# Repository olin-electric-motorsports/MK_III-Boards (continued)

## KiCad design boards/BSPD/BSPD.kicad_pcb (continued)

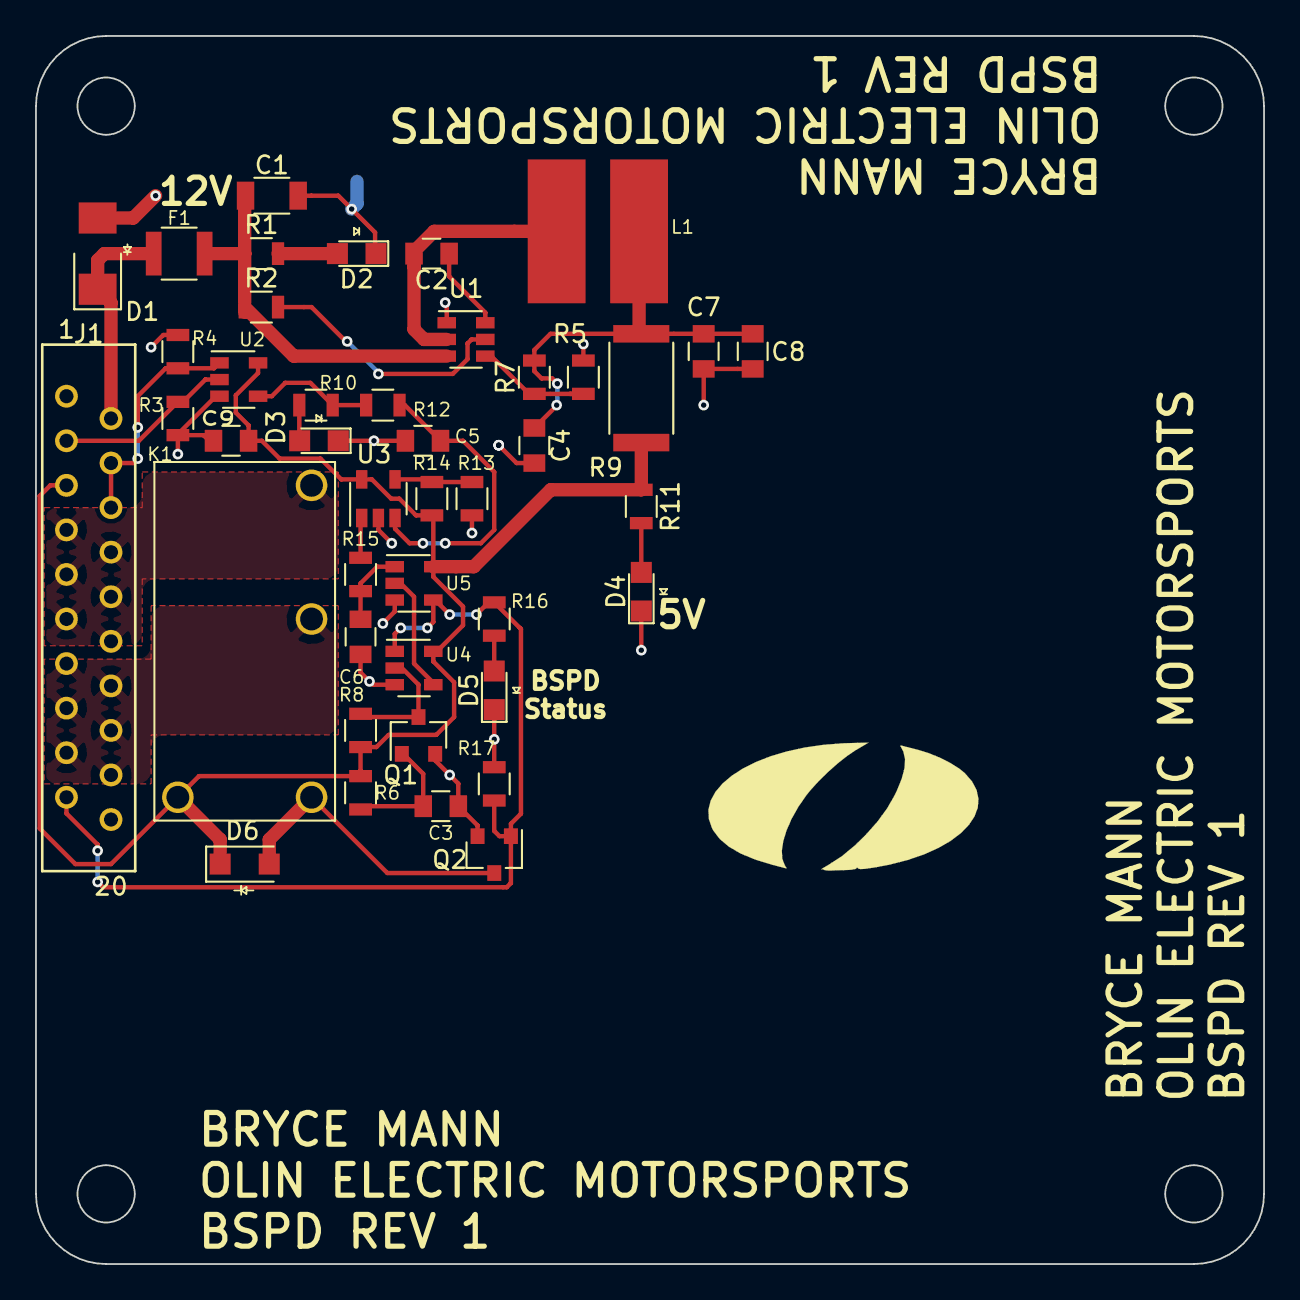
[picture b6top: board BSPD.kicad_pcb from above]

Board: 2 copper layers, 70.0 x 70.0 mm, 43 parts (0 on the bottom side), 27 nets.

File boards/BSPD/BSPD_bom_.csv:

Component,Description,Part,References,Value,Footprint,Quantity Per PCB,Datasheet,Package,MPN,MFN,PurchasingLink,MNF
1,Cap 50V 0.1uF 10% 0805,C_0.1uF,C2 C3 C8 C9,C_0.1uF,C_0805_OEM,4,http://datasheets.avx.com/X7RDielectric.pdf,Value,478-3352-1-ND,Digi-Key,https://www.digikey.com/products/en?keywords=478-3352-1-ND,
2,CAP CER 10UF 10V X5R 0805,C_10uF,C5,C_10uF,C_0805_OEM,1,http://datasheets.avx.com/cx5r.pdf,Value,478-5167-1-ND,Digi-Key,https://www.digikey.com/product-detail/en/avx-corporation/08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,
3,CAP CER 1UF 25V X7R 0805,C_1uF,C6 C7,C_1uF,C_0805_OEM,2,http://datasheets.avx.com/X7RDielectric.pdf,Value,478-10487-1-ND,Digi-Key,https://www.digikey.com/product-detail/en/avx-corporation/08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,
4,Unpolarized capacitor,C_22uF,C1,C_22uF,C_1206_OEM,1,http://www.samsungsem.com/kr/support/product-search/mlcc/__i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,Value,1276-2725-1-ND,Digi-Key,https://www.digikey.com/products/en?keywords=1276-2725-1-ND,
5,CAP CER 47UF 6.3V X5R 0805,C_47uF,C4,C_47uF,C_0805_OEM,1,http://www.yuden.co.jp/productdata/catalog/en/mlcc_all_e.pdf,Value,587-4280-1-ND,Digi-Key,https://www.digikey.com/product-detail/en/taiyo-yuden/JMK212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,
6,DIODE SCHOTTKY 100V 1A SOD123,D_Schottky_SOD123,D6,D_Schottky_SOD123,D_SOD-123W_OEM,1,https://assets.nexperia.com/documents/data-sheet/PMEG10010ELR.pdf,,1727-2394-1-ND,Digi-Key,https://www.digikey.com/product-detail/en/nexperia-usa-inc/P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,
7,DIODE ZENER 18V 5W DO214AA,D_Zener_18V,D1,D_Zener_18V,DO-214AA,1,http://www.mccsemi.com/up_pdf/SMBJ5338B-SMBJ5388B(SMB).pdf,DO-214AA (SMB),SMBJ5355B-TPMSCT-ND,Digi-Key,https://www.digikey.com/products/en?keywords=SMBJ5355B-TPMSCT-ND,
8,LED_0805,LED_0805,D2 D3 D4 D5,LED_0805,LED_0805_OEM,4,http://www.osram-os.com/Graphics/XPic9/00078860_0.pdf,Value,475-1410-1-ND,Digi-Key,https://www.digikey.com/products/en?keywords=475-1410-1-ND,
9,PTC Fuse 16V 500mA,F_500mA_16V,F1,F_500mA_16V,Fuse_1210,1,https://belfuse.com/resources/CircuitProtection/datasheets/0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,Value,507-1786-1-ND,Digi-Key,https://www.digikey.com/product-detail/en/bel-fuse-inc/0ZCH0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,
10,connector micromatch female RA 20,micromatch_female_RA_20,J1,micromatch_female_RA_20,micromatch_female_ra_20,1,,Value,A99490CT-ND,Digi-Key,https://www.digikey.com/product-detail/en/te-connectivity-am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,
11,g5q power relay,G5Q-1A4-DC5-5V,K1,G5Q-1A4-DC5-5V,Relay_SPST_OMRON-G5Q-1A4_OEM,1,http://omronfs.omron.com/en_US/ecb/products/pdf/en-g5q.pdf,,Z3632-ND,Digi-Key,https://www.digikey.com/product-detail/en/omron-electronics-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,
12,Inductor 4.7uH 4.4A,L_4.7uH,L1,L_4.7uH,4.7uH_Inductor_OEM,1,https://product.tdk.com/info/en/documents/wdcatalog/withdraw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,Value,445-6583-1-ND,Digi-Key,https://www.digikey.com/product-detail/en/tdk-corporation/VL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,
13,"60V Vds, 0.115A Id, N-channel MOSFET, SOT-23",SSM3K333R,Q1 Q2,SSM3K333R,SOT-23F,2,https://drive.google.com/drive/folders/0B-V-iZf33Y4GNzhDQTJZanJRbVk,SOT-23-3 Flat Leads,SSM3K333RLFCT-ND,Digi-Key,https://www.digikey.com/product-detail/en/toshiba-semiconduc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,
14,Res 0 2512 3W Jumper,R_0_Jumper,R9,R_0_Jumper,R_2512_OEM,1,http://www.te.com/commerce/DocumentDelivery/DDEController?Ac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,Value,A121322CT-ND,Digi-Key,https://www.digikey.com/products/en?keywords=A121322CT-ND,
15,Res 100k 1%,R_100k,R3 R4 R8,R_100k,R_0805_OEM,3,http://www.yageo.com.tw/exep/pages/download/literatures/PYu-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,Value,311-100KCRCT-ND,Digi-Key,https://www.digikey.com/products/en?keywords=311-100KCRCT-ND,
16,Res 10k 1%,R_10k,R2 R5 R6 R13 R14 R15 R17,R_10k,R_0805_OEM,7,http://www.bourns.com/data/global/pdfs/CRS.pdf,Value,CRS0805-FX-1002ELFCT-ND,Digi-Key,https://www.digikey.com/products/en?keywords=CRS0805-FX-1002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,
17,Res 1k 1%,R_1k,R1,R_1k,R_0805_OEM,1,https://www.seielect.com/Catalog/SEI-rncp.pdf,Value,RNCP0805FTD1K00CT-ND,Digi-Key,https://www.digikey.com/products/en?keywords=RNCP0805FTD1K00CT-ND,
18,Res 200 5%,R_200,R10 R11 R16,R_200,R_0805_OEM,3,https://www.seielect.com/Catalog/SEI-RMCF_RMCP.pdf,Value,RMCF0805JT200RCT-ND,Digi-Key,https://www.digikey.com/products/en?keywords=RMCF0805JT200RCT-ND,
19,Res 55.1k 1%,R_55.1k,R7,R_55.1k,R_0805_OEM,1,http://www.yageo.com.tw/exep/pages/download/literatures/PYu-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,Value,311-51.1KCRCT-ND,Digi-Key,https://www.digikey.com/products/en?keywords=311-51.1KCRCT-ND,
20,Resistor,R_71.5k,R12,R_71.5k,R_0805_OEM,1,http://www.yageo.com/documents/recent/PYu-RC_Group_51_RoHS_L_8.pdf,Value,RC0805FR-0771K5L,Yageo,https://www.digikey.com/product-detail/en/yageo/RC0805FR-077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,
21,Op Amp in 5-pin package,MCP6001,U3,MCP6001,SOT-23-5_OEM,1,http://ww1.microchip.com/downloads/en/DeviceDoc/21733j.pdf,"SC-74A, SOT-753",MCP6001T-I/OT,,https://www.digikey.com/product-detail/en/microchip-technolo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,Microchip Technology
22,Single 2-Input Positive NOR-Gate,SN74LVC1G02,U4 U5,SN74LVC1G02,SOT-23-5_OEM,2,http://www.ti.com/lit/ds/symlink/sn74lvc1g02.pdf,"SC-74A, SOT-753",SN74LVC1G02DBVR,Texas Instruments,https://www.digikey.com/product-detail/en/texas-instruments/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,
23,Single 2-Input Positive-AND Gate,SN74LVC1G08,U2,SN74LVC1G08,SOT-23-5_OEM,1,http://www.ti.com/lit/ds/symlink/sn74lvc1g08.pdf,"SC-74A, SOT-753",SN74LVC1G08DBVR,Texas Instruments,https://www.digikey.com/product-detail/en/texas-instruments/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,
24,4.5V - 17V Input 1A Synchronous Buck Converter,TPS561201,U1,TPS561201,SOT-23-6_OEM,1,http://www.ti.com/lit/ds/symlink/tps561201.pdf,Value,TPS561201,Digi-Key,https://www.digikey.com/products/en?keywords=296-46928-1-ND,





Component Groups:,24
Component Count:,43
Fitted Components:,43
Number of PCBs:,1
Total components:,43
Schematic Version:,
Schematic Date:,
BoM Date:,Mon 05 Feb 2018 09:23:43 PM EST
Schematic Source:,/home/bryce/Desktop/Formula/MK_III-Boards/boards/BSPD/BSPD.sch
KiCad Version:,Eeschema 4.0.2+dfsg1-stable

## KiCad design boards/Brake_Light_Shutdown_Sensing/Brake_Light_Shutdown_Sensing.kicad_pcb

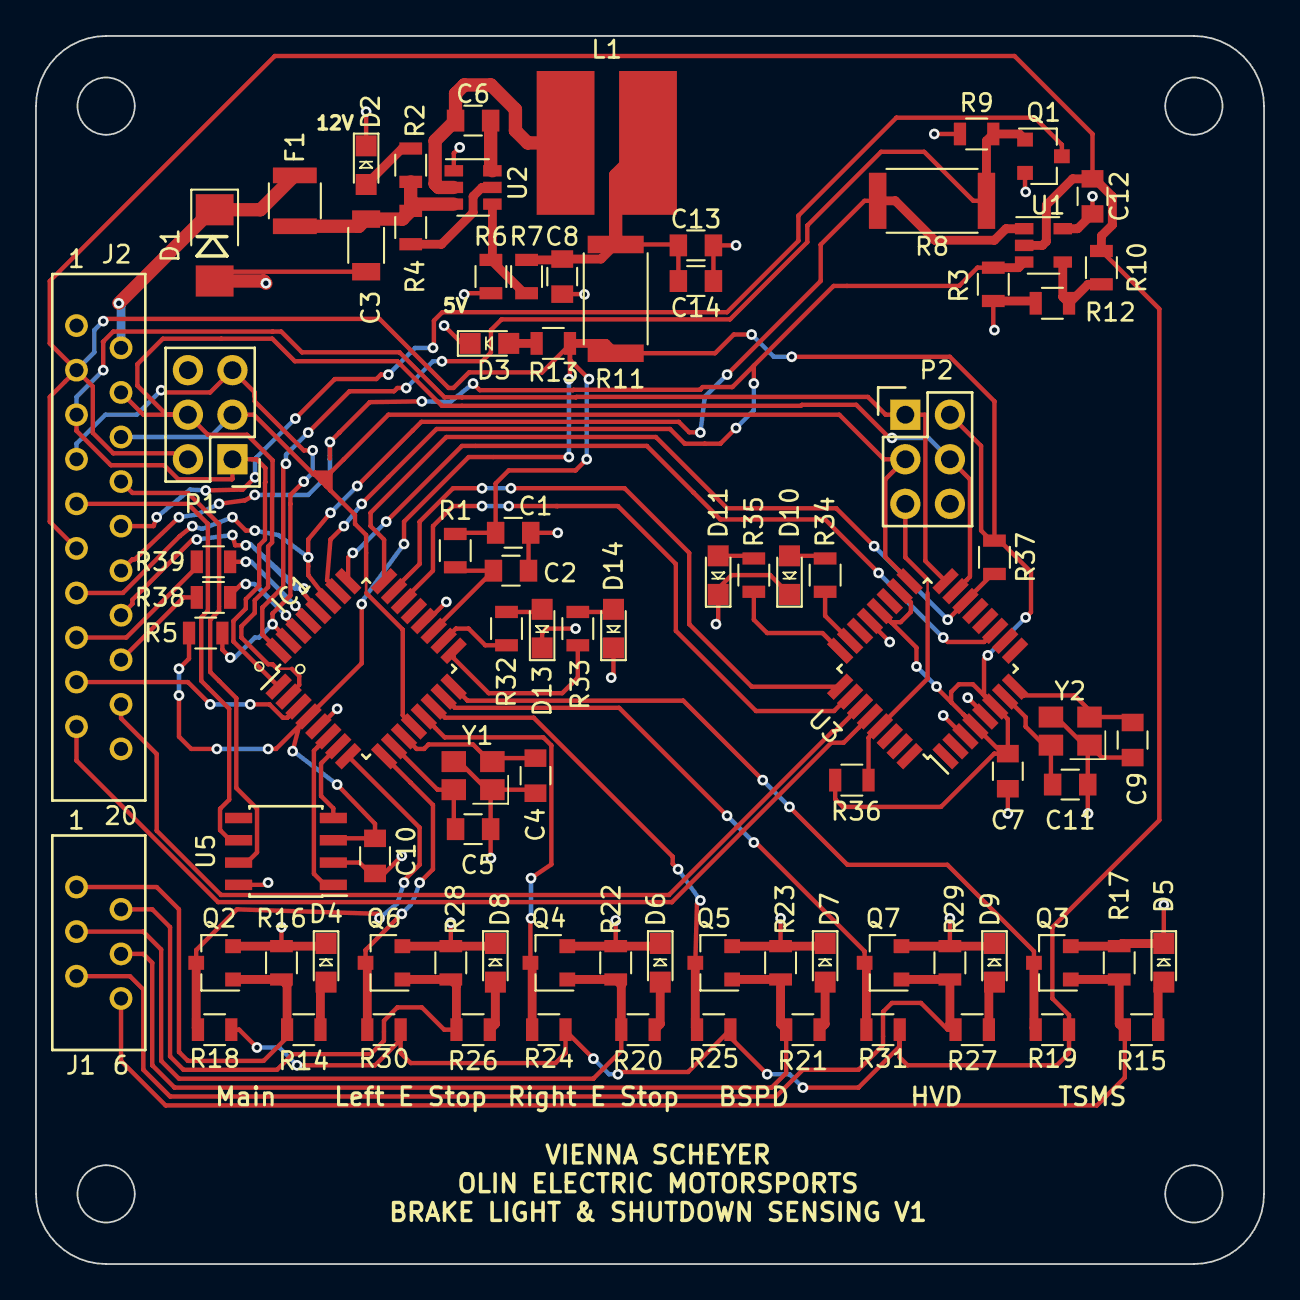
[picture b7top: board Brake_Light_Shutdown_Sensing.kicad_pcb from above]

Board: 2 copper layers, 70.0 x 70.0 mm, 86 parts (0 on the bottom side), 68 nets.

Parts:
C1, C6, C7, C10, C12, C14: C_0.1uF; C_0805_OEM
C2: C_100pF; C_0805_OEM
C3: C_22uF; C_1206_OEM
C4, C5, C9, C11: C_30pF; C_0805_OEM
C8: C_47uF; C_0805_OEM
C13: C_1uF; C_0805_OEM
D1: D_Zener_18V; DO-214AA
D2, D3, D4, D5, D6, D7, D8, D9, D10, D11, D13, D14: LED_0805; LED_0805_OEM
F1: F_500mA_16V; Fuse_1210
IC1: ATMEGA16M1; TQFP-32_7x7mm_Pitch0.8mm
J1: micromatch_female_RA_6; micromatch_female_ra_6
J2: micromatch_female_RA_20; micromatch_female_ra_20
L1: L_4.7uH; 4.7uH_Inductor_OEM
P1, P2: CONN_02X03; Pin_Header_Straight_2x03
Q1, Q2, Q3, Q4, Q5, Q6, Q7: SSM3K333R; SOT-23F
R1: R_100; R_0805_OEM
R2: R_1K; R_0805_OEM
R3, R4, R5, R6, R9, R10, R12, R18, R19, R24, R25, R30, R31, R36, R37: R_10k; R_0805_OEM
R7: 55.1K; R_0805_OEM
R8, R11: R_0_Jumper; R_2512_OEM
R13, R32, R33, R34, R35, R38, R39: R_200; R_0805_OEM
R14, R15, R20, R21, R26, R27: R_1k; R_0805_OEM
R16, R17, R22, R23, R28, R29: R_100k; R_0805_OEM
U1: MCP6001RT; SOT-23-5_OEM
U2: TPS561201; SOT-23-6_OEM
U3: ATMEGA328P-AU; TQFP-32_7x7mm_Pitch0.8mm
U5: CAN_Transceiver; SOIC-8_3.9x4.9mm_Pitch1.27mm_OEM
Y1, Y2: Crystal_SMD; Crystal_SMD_FA238

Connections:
+5V: C1.1, C7.1, C10.1, C12.1, IC1.4, J2.3, J2.11, P1.2, P2.2, R1.1, R5.1, R10.2, R11.1, R13.1, R18.1, R19.1, R24.1, R25.1, R30.1, R31.1, R36.1, R37.1, U1.2, U3.4, U3.6, U3.18, U3.20, U5.3
+12V: D1.1, F1.1, J2.2
/Analog_Brake_Sense: IC1.28, J2.14
/BSPD_Out: IC1.27, J2.13, R8.2, U1.1
/BSPD_Pin: IC1.14, Q5.3, R25.2
/BSPD_Sense: J1.4, Q5.1, R21.1, R23.1
/BSPD_Stat_Out: IC1.3, J2.17
/Brake_Light_Gate: IC1.32, Q1.1, R8.1, R9.1
/Brake_Light_LSD: J2.10, Q1.3
/Brake_Switch-: IC1.26, J2.12, R3.2, U1.3
/CAN_high: J2.8, U5.7
/CAN_low: J2.9, U5.6
/HVD_Pin: IC1.15, Q7.3, R31.2
/HVD_Sense: J1.5, Q7.1, R27.1, R29.1
/LED5: R34.1, U3.23
/LED6: R35.1, U3.24
/LED_1: J2.15, R39.1
/LED_2: J2.16, R38.1
/LED_3: IC1.18, R32.1
/LED_4: IC1.17, R33.1
/L_E-Stop_Pin: IC1.9, Q6.3, R30.2
/L_E-Stop_Sense: J1.2, Q6.1, R26.1, R28.1
/MISO: IC1.1, J2.5, P1.1, P2.1, U3.16
/MOSI: IC1.2, J2.4, P1.4, P2.4, U3.15
/Main_Sense: J1.1, Q2.1, R14.1, R16.1
/Main_Shut_Fuse: IC1.8, Q2.3, R18.2
/RESET: IC1.31, J2.7, P1.5, R5.2
/RST32: P2.5, R36.2, U3.29
/RXCAN: IC1.7, U5.4
/R_E-Stop_Sense: J1.3, Q4.1, R20.1, R22.1
/R_EStop_Pin: IC1.13, Q4.3, R24.2
/SCK: IC1.12, J2.6, P1.3, P2.3, U3.17
/SCL: J2.19, U3.28
/SDA: J2.18, U3.27
/TSMS_Pin: IC1.16, Q3.3, R19.2
/TSMS_Sense: J1.6, Q3.1, R15.1, R17.1
/TXCAN: IC1.6, U5.1
/XTAL1: C11.1, U3.7, Y2.3
/XTAL2: C9.1, U3.8, Y2.1
/data1: IC1.24, R37.2, U3.14
/data2: IC1.22, U3.26
/data3: IC1.23, U3.25
/data4: IC1.25, U3.11
GND: C1.2, C2.2, C3.2, C4.2, C5.2, C7.2, C8.2, C9.2, C10.2, C11.2, C12.2, C13.2, C14.2, D1.2, D2.1, D3.1, D4.1, D5.1, D6.1, D7.1, D8.1, D9.1, D10.1, D11.1, D13.1, D14.1, IC1.5, IC1.20, J2.1, P1.6, P2.6, Q1.2, Q2.2, Q3.2, Q4.2, Q5.2, Q6.2, Q7.2, R3.1, R6.2, R9.2, R12.1, R16.2, R17.2, R22.2, R23.2, R28.2, R29.2, U1.5, U2.1, U3.3, U3.5, U3.21, U5.2, U5.8, Y1.2, Y1.4, Y2.2, Y2.4
unnamed: C2.1, IC1.19, R1.2
unnamed: C3.1, F1.2, R2.1, R4.1, U2.3
unnamed: C4.1, IC1.11, Y1.1
unnamed: C5.1, IC1.10, Y1.3
unnamed: C6.1, U2.6
unnamed: C6.2, L1.1, U2.2
unnamed: C8.1, C13.1, C14.1, L1.2, R7.2, R11.2
unnamed: D2.2, R2.2
unnamed: D3.2, R13.2
unnamed: D4.2, R14.2
unnamed: D5.2, R15.2
unnamed: D6.2, R20.2
unnamed: D7.2, R21.2
unnamed: D8.2, R26.2
unnamed: D9.2, R27.2
unnamed: D10.2, R34.2
unnamed: D11.2, R35.2
unnamed: D13.2, R32.2
unnamed: D14.2, R33.2
unnamed: IC1.29, R39.2
unnamed: IC1.30, R38.2
unnamed: R4.2, U2.5
unnamed: R6.1, R7.1, U2.4
unnamed: R10.1, R12.2, U1.4

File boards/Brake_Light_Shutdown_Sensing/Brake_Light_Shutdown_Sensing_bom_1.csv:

Subsystem,MFN,MPN,Description,Quantity Per PCB,Component,,Part,References,Value,Footprint,,Datasheet,Package,,,PurchasingLink,Purchase_Link
Brake_Light_Shutdown_Sensing,Digi-Key,478-3352-1-ND,Cap 50V 0.1uF 10% 0805,6,1,,C_0.1uF,C1 C6 C7 C10 C12 C14,C_0.1uF,C_0805_OEM,,http://datasheets.avx.com/X7RDielectric.pdf,Value,,,https://www.digikey.com/products/en?keywords=478-3352-1-ND,
Brake_Light_Shutdown_Sensing,Digi-Key,399-1122-1-ND,Cap 50V 100pF 5% 0805,1,2,,C_100pF,C2,C_100pF,C_0805_OEM,,https://content.kemet.com/datasheets/KEM_C1003_C0G_SMD.pdf,Value,,,https://www.digikey.com/product-detail/en/kemet/C0805C101J5G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,
Brake_Light_Shutdown_Sensing,Digi-Key,478-10487-1-ND,CAP CER 1UF 25V X7R 0805,1,3,,C_1uF,C13,C_1uF,C_0805_OEM,,http://datasheets.avx.com/X7RDielectric.pdf,Value,,,https://www.digikey.com/product-detail/en/avx-corporation/08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,
Brake_Light_Shutdown_Sensing,Digi-Key,1276-2725-1-ND,Unpolarized capacitor,1,4,,C_22uF,C3,C_22uF,C_1206_OEM,,http://www.samsungsem.com/kr/support/product-search/mlcc/__i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,Value,,,https://www.digikey.com/products/en?keywords=1276-2725-1-ND,
Brake_Light_Shutdown_Sensing,Digi-Key,1276-1130-1-ND,Cap 50V 30pF 5% 0805,4,5,,C_30pF,C4 C5 C9 C11,C_30pF,C_0805_OEM,,https://media.digikey.com/pdf/Data%20Sheets/Samsung%20PDFs/C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,Value,,,https://www.digikey.com/product-detail/en/samsung-electro-me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,
Brake_Light_Shutdown_Sensing,Digi-Key,587-4280-1-ND,CAP CER 47UF 6.3V X5R 0805,1,6,,C_47uF,C8,C_47uF,C_0805_OEM,,http://www.yuden.co.jp/productdata/catalog/en/mlcc_all_e.pdf,Value,,,https://www.digikey.com/product-detail/en/taiyo-yuden/JMK212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,
Brake_Light_Shutdown_Sensing,Digi-Key,SMBJ5355B-TPMSCT-ND,DIODE ZENER 18V 5W DO214AA,1,7,,D_Zener_18V,D1,D_Zener_18V,DO-214AA,,http://www.mccsemi.com/up_pdf/SMBJ5338B-SMBJ5388B(SMB).pdf,DO-214AA (SMB),,,https://www.digikey.com/products/en?keywords=SMBJ5355B-TPMSCT-ND,
Brake_Light_Shutdown_Sensing,Digi-Key,475-1410-1-ND,LED_0805,12,8,,LED_0805,D2 D3 D4 D5 D6 D7 D8 D9 D10 D11 D13 D14,LED_0805,LED_0805_OEM,,http://www.osram-os.com/Graphics/XPic9/00078860_0.pdf,Value,,,https://www.digikey.com/products/en?keywords=475-1410-1-ND,
Brake_Light_Shutdown_Sensing,Digi-Key,507-1786-1-ND,PTC Fuse 16V 500mA,1,9,,F_500mA_16V,F1,F_500mA_16V,Fuse_1210,,https://belfuse.com/resources/CircuitProtection/datasheets/0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,Value,,,https://www.digikey.com/product-detail/en/bel-fuse-inc/0ZCH0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,
Brake_Light_Shutdown_Sensing,Digi-Key,ATMEGA16M1-AU-ND,"TQFP32, 16k Flash, 1k SRAM, 512B EEPROM, CAN",1,10,,ATMEGA16M1,IC1,ATMEGA16M1,TQFP-32_7x7mm_Pitch0.8mm,,http://www.atmel.com/Images/Atmel-8209-8-bit%20AVR%20ATmega1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,Value,,,https://www.digikey.com/product-detail/en/atmel/ATMEGA16M1-A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,
Brake_Light_Shutdown_Sensing,Digi-Key,A99490CT-ND,connector micromatch female RA 20,1,11,,micromatch_female_RA_20,J2,micromatch_female_RA_20,micromatch_female_ra_20,,,Value,,,https://www.digikey.com/product-detail/en/te-connectivity-am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,
Brake_Light_Shutdown_Sensing,Digi-Key,A99483CT-ND,connector micromatch female RA 6,1,12,,micromatch_female_RA_6,J1,micromatch_female_RA_6,micromatch_female_ra_6,,,Value,,,https://www.digikey.com/product-detail/en/te-connectivity-am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,
Brake_Light_Shutdown_Sensing,Digi-Key,445-6583-1-ND,Inductor 4.7uH 4.4A,1,13,,L_4.7uH,L1,L_4.7uH,4.7uH_Inductor_OEM,,https://product.tdk.com/info/en/documents/wdcatalog/withdraw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,Value,,,https://www.digikey.com/product-detail/en/tdk-corporation/VL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,
Brake_Light_Shutdown_Sensing,Digi-Key,609-3234-ND,"Connector, double row, 02x03",2,14,,CONN_02X03,P1 P2,CONN_02X03,Pin_Header_Straight_2x03,,http://portal.fciconnect.com/Comergent//fci/drawing/67996.pdf,Value,,,https://www.digikey.com/product-detail/en/amphenol-fci/67997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,
Brake_Light_Shutdown_Sensing,Digi-Key,SSM3K333RLFCT-ND,"60V Vds, 0.115A Id, N-channel MOSFET, SOT-23",7,15,,SSM3K333R,Q1 Q2 Q3 Q4 Q5 Q6 Q7,SSM3K333R,SOT-23F,,file:///home/sherrieshen/Downloads/SSM3K333R_datasheet_en_20140301.pdf,SOT-23-3 Flat Leads,,,https://www.digikey.com/product-detail/en/toshiba-semiconduc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,https://www.digikey.com/product-detail/en/toshiba-semiconduc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
Brake_Light_Shutdown_Sensing,Digi-Key,311-51.1KCRCT-ND,Res 55.1k 1%,1,16,,R_55.1k,R7,55.1K,R_0805_OEM,,http://www.yageo.com.tw/exep/pages/download/literatures/PYu-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,Value,,,https://www.digikey.com/products/en?keywords=311-51.1KCRCT-ND,
Brake_Light_Shutdown_Sensing,Digi-Key,A121322CT-ND,Res 0 2512 3W Jumper,2,17,,R_0_Jumper,R8 R11,R_0_Jumper,R_2512_OEM,,http://www.te.com/commerce/DocumentDelivery/DDEController?Ac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,Value,,,https://www.digikey.com/products/en?keywords=A121322CT-ND,
Brake_Light_Shutdown_Sensing,Digi-Key,RNCP0805FTD100RCT-ND,Res 100 1%,1,18,,R_100,R1,R_100,R_0805_OEM,,https://www.seielect.com/Catalog/SEI-rncp.pdf,Value,,,https://www.digikey.com/products/en?keywords=RNCP0805FTD100RCT-ND,
Brake_Light_Shutdown_Sensing,Digi-Key,311-100KCRCT-ND,Res 100k 1%,6,19,,R_100k,R16 R17 R22 R23 R28 R29,R_100k,R_0805_OEM,,http://www.yageo.com.tw/exep/pages/download/literatures/PYu-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,Value,,,https://www.digikey.com/products/en?keywords=311-100KCRCT-ND,
Brake_Light_Shutdown_Sensing,Digi-Key,CRS0805-FX-1002ELFCT-ND,Res 10k 1%,15,20,,R_10k,R3 R4 R5 R6 R9 R10 R12 R18 R19 R24 R25 R30 R31 R36 R37,R_10k,R_0805_OEM,,http://www.bourns.com/data/global/pdfs/CRS.pdf,Value,,,https://www.digikey.com/products/en?keywords=CRS0805-FX-1002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,
Brake_Light_Shutdown_Sensing,Digi-Key,RNCP0805FTD1K00CT-ND,Res 1k 1%,7,21,,R_1k,R2 R14 R15 R20 R21 R26 R27,R_1K,R_0805_OEM,,https://www.seielect.com/Catalog/SEI-rncp.pdf,Value,,,https://www.digikey.com/products/en?keywords=RNCP0805FTD1K00CT-ND,
Brake_Light_Shutdown_Sensing,Digi-Key,RMCF0805JT200RCT-ND,Res 200 5%,7,22,,R_200,R13 R32 R33 R34 R35 R38 R39,R_200,R_0805_OEM,,https://www.seielect.com/Catalog/SEI-RMCF_RMCP.pdf,Value,,,https://www.digikey.com/products/en?keywords=RMCF0805JT200RCT-ND,
Brake_Light_Shutdown_Sensing,,,"TQFP32, 16k Flash, 1kB SRAM, 512B EEPROM",1,23,,ATMEGA328P-AU,U3,ATMEGA328P-AU,TQFP-32_7x7mm_Pitch0.8mm,,http://www.atmel.com/images/atmel-8271-8-bit-avr-microcontro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,,,,,
Brake_Light_Shutdown_Sensing,Digi-Key,MCP2561-E/SN-ND,"High-Speed CAN Transceiver, 1Mbps, 5V supply, SPLIT pin, -40C to +125C, SOIC8 package",1,24,,CAN_Transceiver,U5,CAN_Transceiver,SOIC-8_3.9x4.9mm_Pitch1.27mm_OEM,,http://www.microchip.com/mymicrochip/filehandler.aspx?ddocna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,Value,,,https://www.digikey.com/products/en?keywords=mcp2561-e%2Fsn,
Brake_Light_Shutdown_Sensing,Digi-Key,MCP6001RT-I/OTCT-ND,IC OPAMP GP 1MHZ RRO SOT23-5  1.8-6V,1,25,,MCP6001RT,U1,MCP6001RT,SOT-23-5_OEM,,http://ww1.microchip.com/downloads/en/DeviceDoc/21733j.pdf,,,,https://www.digikey.com/product-detail/en/microchip-technolo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,
Brake_Light_Shutdown_Sensing,Digi-Key,TPS561201,4.5V - 17V Input 1A Synchronous Buck Converter,1,26,,TPS561201,U2,TPS561201,SOT-23-6_OEM,,http://www.ti.com/lit/ds/symlink/tps561201.pdf,Value,,,https://www.digikey.com/products/en?keywords=296-46928-1-ND,
Brake_Light_Shutdown_Sensing,Digi-Key,SER3686CT-ND,"Two pin crystal, two ground/package pins (pin2 and 3) small symbol",2,27,,Crystal_SMD,Y1 Y2,Crystal_SMD,Crystal_SMD_FA238,,https://support.epson.biz/td/api/doc_check.php?dl=brief_FA-2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,Value,,,https://www.digikey.com/products/en?keywords=SER3686CT-ND,
,,,,,,,,,,,,,,,,,
,,,,,,,,,,,,,,,,,
,,,,,,,,,,,,,,,,,
,,,,,,,,,,,,,,,,,
,,,,,,,,,,,,,,,,,
,,,27,,Component Groups:,,,,,,,,,,,,
,,,86,,Component Count:,,,,,,,,,,,,
,,,86,,Fitted Components:,,,,,,,,,,,,
,,,1,,Number of PCBs:,,,,,,,,,,,,
,,,86,,Total components:,,,,,,,,,,,,
,,,1,,Schematic Version:,,,,,,,,,,,,
,,,2017-10-19,,Schematic Date:,,,,,,,,,,,,
,,,Mon 19 Feb 2018 07:24:46 PM EST,,BoM Date:,,,,,,,,,,,,
,,,/home/vscheyer/Desktop/Formula/MK_III-Boards/boards/Brake_Light_Shutdown_Sensing/Brake_Light_Shutdown_Sensing.sch,,Schematic Source:,,,,,,,,,,,,
,,,Eeschema 4.0.7-e2-6376~58~ubuntu16.04.1,,KiCad Version:,,,,,,,,,,,,
